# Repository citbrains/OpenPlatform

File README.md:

# OpenPlatform
Open Platform Humanoid Robot  

We are developing an open platform humanoid robot for the RoboCup Humanoid League.  
We aim to develop a robust robot system that helps the experiment on the real robot.  
The original robot was designed by Shimoyoshi.

GankenKun ver.3 (2020/11/22)

### Prizes
2019 RoboCup 4on4 3rd, Technical Challenge 2nd, Drop In Challenge 2nd  
2018 RoboCup 4on4 3rd, Technical Challenge 1st  
2017 RoboCup 4on4 3rd, Technical Challenge 1st  

### VIDEO
https://www.youtube.com/playlist?list=PLB7_jZwkBJdQZTIP_5HFZ_qUzT54mZ3Gq

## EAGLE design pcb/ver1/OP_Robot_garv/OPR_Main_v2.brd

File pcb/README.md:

# PCB data

We design the circuit using EAGLE.

## Version 1

`ver1/OP_Robot_garv`: This circuit is the doughterboard for Raspberry Pi.  
For preview, see `OPR_Main_v2_board.pdf` and `OPR_Main_v2_schematics.pdf`.  

## Version 3

`ver3/power_circuit`: This circuit is the power supply switching circuit.  

## Bugs

If you find a bug please let me know by opening an issue.

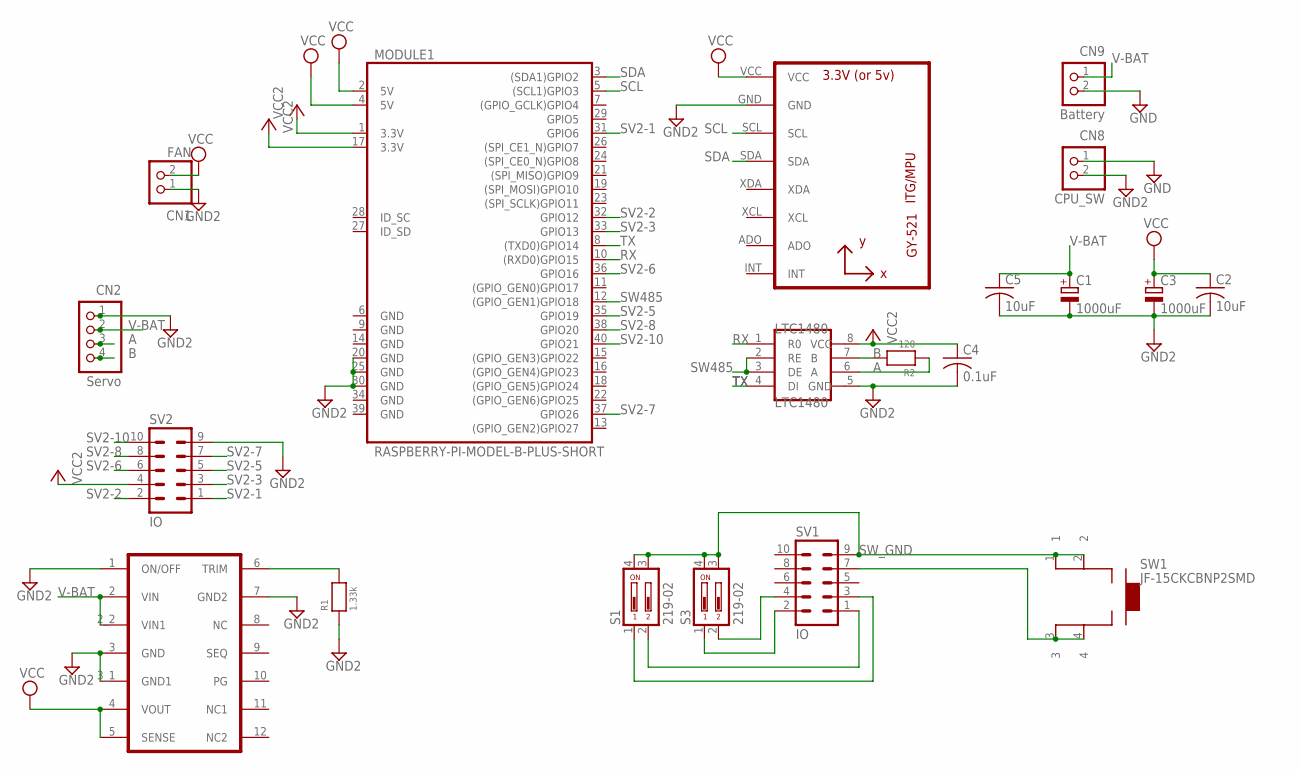
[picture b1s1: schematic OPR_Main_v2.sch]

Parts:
C1, C3: 1000uF; E5-10,5
C2, C5: 10uF; C3225
C4: 0.1uF; C2012
CN1: FAN; B2B-XH-A
CN2: Servo; S4B-XH-A
CN8: CPU_SW; B2P-VH
CN9: Battery; B2P-VH
LTC1480: LTC1480; SOIC-8
MODULE1: RASPBERRY-PI-MODEL-B-PLUS-SHORT
R1: 1.33k; 0805_NOTHERMALS
R2: 120; 0805_NOTHERMALS
S1, S3: 219-02; CTS-219-02
SV1, SV2: IO; ML10
SW1: JF-15CKCBNP2SMD; JF-15CKCBNP2-SMD
U1: GY-521MPU6050; GY-521
U$3: OKL-T/W-12N-C; OKL_T6_W12

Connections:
A: CN2.3, LTC1480.6 (A), R2.1
B: CN2.4, LTC1480.7 (B), R2.2
GND: CN8.1, CN9.2
GND2: C1.-, C2.2, C3.-, C4.2, C5.2, CN1.1, CN2.1, CN8.2, LTC1480.5 (GND), MODULE1.20 (GND), MODULE1.25 (GND), MODULE1.30 (GND), R1.1, SV2.9, U1.GND, U$3.1 (ON/OFF), U$3.3 (GND), U$3.3_1 (GND1), U$3.7 (GND2)
unnamed: R1.2, U$3.6 (TRIM)
unnamed: S3.2, SV1.4
unnamed: SV1.7, SW1.3, SW1.4
unnamed: S3.1, SV1.2
unnamed: S1.2, SV1.1
unnamed: S1.1, SV1.3
RX: LTC1480.1 (R0), MODULE1.10 ((RXD0)GPIO15)
SCL: MODULE1.5 ((SCL1)GPIO3), U1.SCL
SDA: MODULE1.3 ((SDA1)GPIO2), U1.SDA
SV2-1: MODULE1.31 (GPIO6), SV2.1
SV2-2: MODULE1.32 (GPIO12), SV2.2
SV2-3: MODULE1.33 (GPIO13), SV2.3
SV2-5: MODULE1.35 (GPIO19), SV2.5
SV2-6: MODULE1.36 (GPIO16), SV2.6
SV2-7: MODULE1.37 (GPIO26), SV2.7
SV2-8: MODULE1.38 (GPIO20), SV2.8
SV2-10: MODULE1.40 (GPIO21), SV2.10
SW485: LTC1480.2 (RE), LTC1480.3 (DE), MODULE1.12 ((GPIO_GEN1)GPIO18)
SW_GND: S1.3, S1.4, S3.3, S3.4, SV1.9, SW1.1, SW1.2
TX: LTC1480.4 (DI), MODULE1.8 ((TXD0)GPIO14)
V-BAT: C1.+, C5.1, CN2.2, CN9.1, U$3.2 (VIN), U$3.2_2 (VIN1)
VCC: C2.1, C3.+, CN1.2, MODULE1.2 (5V), MODULE1.4 (5V), U1.VCC, U$3.4 (VOUT), U$3.5 (SENSE)
VCC2: C4.1, LTC1480.8 (VCC), MODULE1.1 (3.3V), MODULE1.17 (3.3V), SV2.4

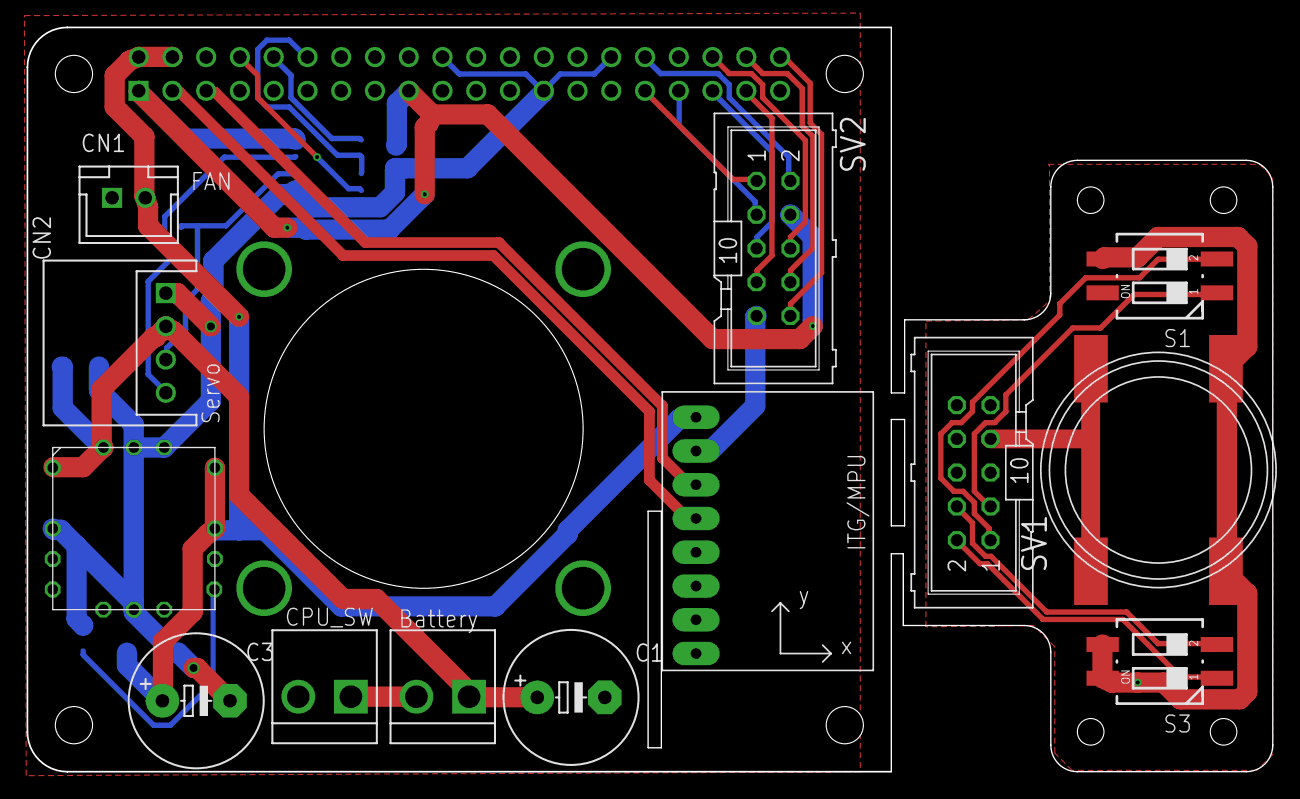
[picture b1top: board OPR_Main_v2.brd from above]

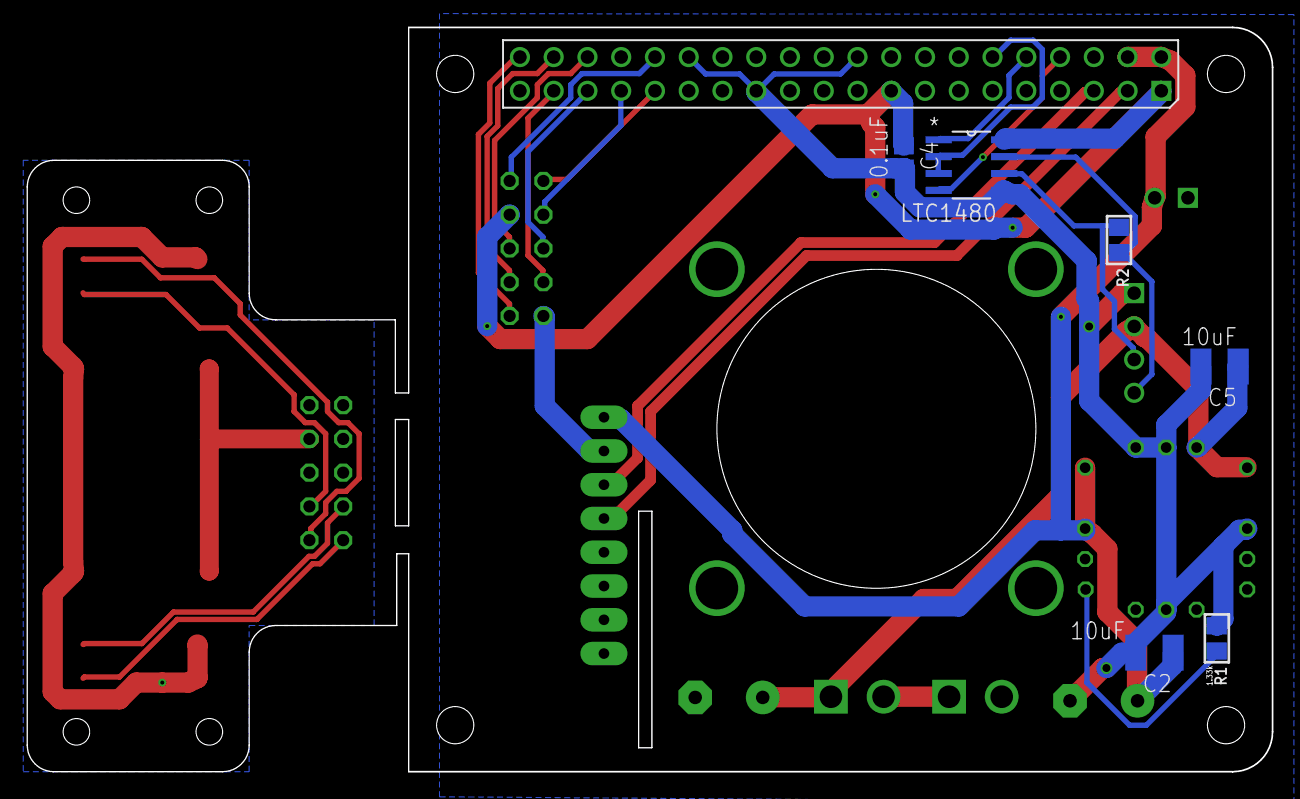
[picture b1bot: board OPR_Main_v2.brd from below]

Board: 2 copper layers, 93.7 x 56.0 mm, 20 parts (6 on the bottom side), 27 nets.

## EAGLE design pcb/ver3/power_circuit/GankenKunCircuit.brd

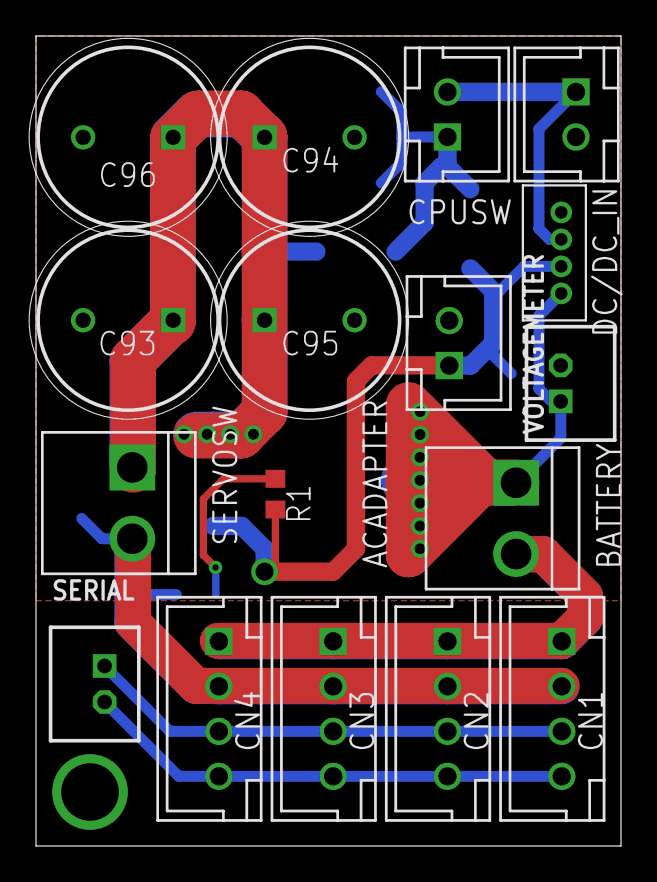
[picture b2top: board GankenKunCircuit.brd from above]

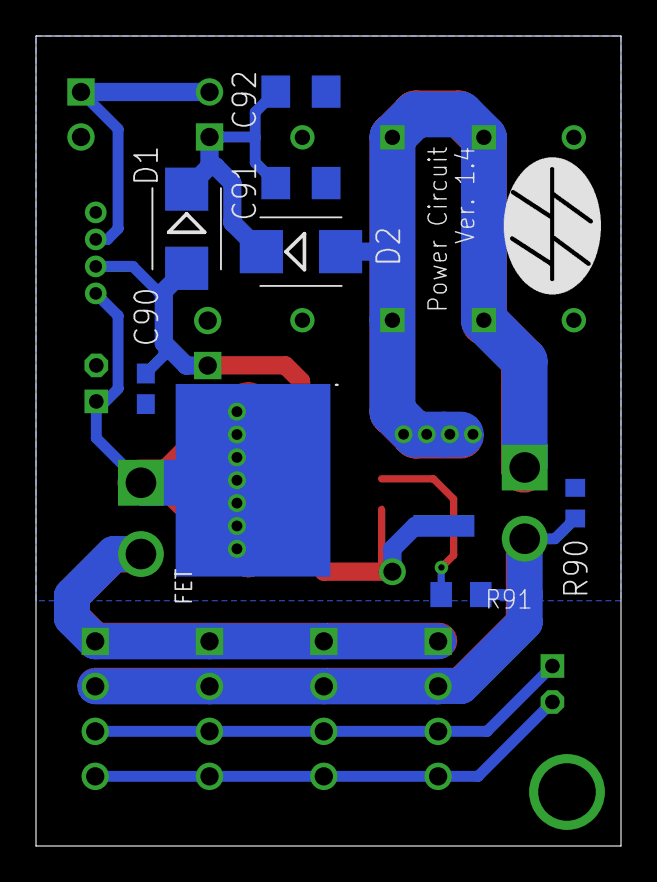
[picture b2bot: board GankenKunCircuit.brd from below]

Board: 2 copper layers, 32.5 x 45.0 mm, 25 parts (8 on the bottom side), 9 nets.

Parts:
ACADAPTER: B2B-XH-A
BATTERY: B2P-VH
C90: 0.1u; C1608
C91, C92: 10u; C3216
C93, C94, C95, C96: 35SEPF120M; CAPPRD500W65D1000H1350
CN1, CN2, CN3, CN4: B4B-XH-A
CPUSW: B2B-XH-A
D1, D2: SMB
DC/DC_IN: B2B-XH-A
FET: SUM110P06-07L; TO-263-2
OTHER_BOARD: B4B-ZR
R1, R90: 10k; R0603
R91: VARISTORCN0805; CT/CN0805
SERIAL: B2B-PH-K
SERVOSW: B2P-VH
VOLTAGEMETER: B2B-PH-K

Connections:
GND: ACADAPTER.2, BATTERY.2, C90.2, C91.2, C92.2, C93.2, C94.2, C95.2, C96.2, CN1.1, CN2.1, CN3.1, CN4.1, DC/DC_IN.2, OTHER_BOARD.4, R1.1, R90.1, R91.2, VOLTAGEMETER.2
unnamed: BATTERY.1, FET.4, OTHER_BOARD.1, VOLTAGEMETER.1
unnamed: C93.1, C94.1, C95.1, C96.1, D2.A, FET.3, SERVOSW.1
unnamed: C91.1, C92.1, CPUSW.1, D1.C, D2.C
unnamed: ACADAPTER.1, C90.1, D1.A, FET.1, OTHER_BOARD.2, R1.2
unnamed: CPUSW.2, DC/DC_IN.1, OTHER_BOARD.3
RS485_A: CN1.3, CN2.3, CN3.3, CN4.3, SERIAL.1
RS485_B: CN1.4, CN2.4, CN3.4, CN4.4, SERIAL.2
VCC: CN1.2, CN2.2, CN3.2, CN4.2, R90.2, R91.1, SERVOSW.2

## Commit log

2016-07-06 gpio_serial
2016-07-06 OSversion
2016-07-07 mpu-6050sample
2016-12-19 サーボとの通信テスト用プログラム
2016-12-19 added .DS_store
2016-12-30 Open Platform ver.1
2016-12-30 Inventor2016 CAD files
2017-01-13 Create electronics
2017-04-19 Change for watching the ball near the feet
2017-04-27 add image
2017-08-26 Add V-Rep simulation model file
2017-12-10 long_arm
2017-12-10 long_head
2017-12-11 はめ込み穴を0.1mm広げる
2018-04-02 convert necessary parts to stl
2018-04-02 added arm xacro
2018-04-02 completed upper body
2018-04-03 added lower part
2018-04-03 added height
2018-04-16 fix name
2018-05-09 added gazebo plugin and effort transmission
2018-05-09 added position and joint trajectory control and pid for mimic
2018-05-09 change frame
2018-05-09 fix bug
2018-05-11 rename gk_* to opr_*
2018-05-11 added info
2018-10-14 Added OpenPlatform_ver3_0
2018-10-14 Added stl file
2018-10-22 Fixed Head
2018-10-23 Added spimplified model
2018-10-25 Added アンテナパーツ_MIR
2018-10-29 Minor fixes
2018-11-01 Fix link relationship
2018-11-05 Fix miss
2019-03-24 Add parts status
2019-03-24 Fix arms
2019-05-13 large_foot_for_RoboCup2019
2019-05-14 Add torso subframe 1_4_MIR #47
2019-06-16 foot for RoboCup2019
2019-06-16 assemble about foot
2019-06-23 Cockpit camera cable wiring
2019-09-02 add power circuit board and schematics data
2019-09-03 update pcb data
2019-09-03 add readme for pcb data
2019-09-10 added basic urdf model
2019-09-10 clean up version1 files
2019-09-10 sort sensor file
2019-09-10 fix indent
2019-09-13 Change batterybox
2019-09-13 Antenna change
2019-09-13 Add camera cable assist
2019-09-13 change joint name
2019-09-13 Add TPU bumpers
2019-09-13 Fix parameters
2019-09-13 Fix parameter of 足裏_メインフレーム_2_3
2020-10-14 Camera 3D printed parts compatible with L-shaped USB cable
2020-11-14 add mente_stand
    メンテナンス台のモデルを追加しました
2020-11-24 固定方法をねじ式からスライド式に変更
2021-01-02 add hole

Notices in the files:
parts and their libraries:
microbuilder: This work is placed in the public domain, and may be freely used for commercial and non-commercial work with the following conditions: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
jst-ph: Copyright (C) 2016, Bob Starr
